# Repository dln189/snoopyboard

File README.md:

# Snoopyboard

Snoopyboard is a 4 key macro pad with a rotary encoder as well as an OLED Display, uses QMK firmware

## Features:

- 4 Mechanical keys arranged in an arrow key formation
- EC11 Rotary Encoder, controlling volume on rotation an muting when pressed
- 128x32 OLED display (still needs to be programmed whoops!)
- Seeed XIAO RP2040
- Custom PCB

## Case

The base connects to the top with 4 M3x16mm Screws, printed in 3 pieces total. (modeled in Fusion360)

Expanded view of the case: 

##PCB Design

Made in Kicad

Scematic:

PCB:

## Firmware

Snoopyboard uses QMK firmware for everything. 

- the rotary encoder changes volume. press to mute
- The 4 keys currently pause/play music, skip or go to previous song and presses right ctrl (my keybind for muting on discord)
- The OLED will be snoopy but that is currently not finished

## BOM:
Here should be everything you need to make this hackpad

- 4x Cherry MX Switches
- 4x DSA Keycaps
- 4x M3x5x4 Heatset inserts
- 4x M3x16mm SHCS Bolts
- 1x 0.91" 128x32 OLED Display
- 1x EC11 Rotary Encoder
- 1x XIAO RP2040
- 1x Case (3 printed parts)

I'm still actively working on this project so expect more stuff soon!

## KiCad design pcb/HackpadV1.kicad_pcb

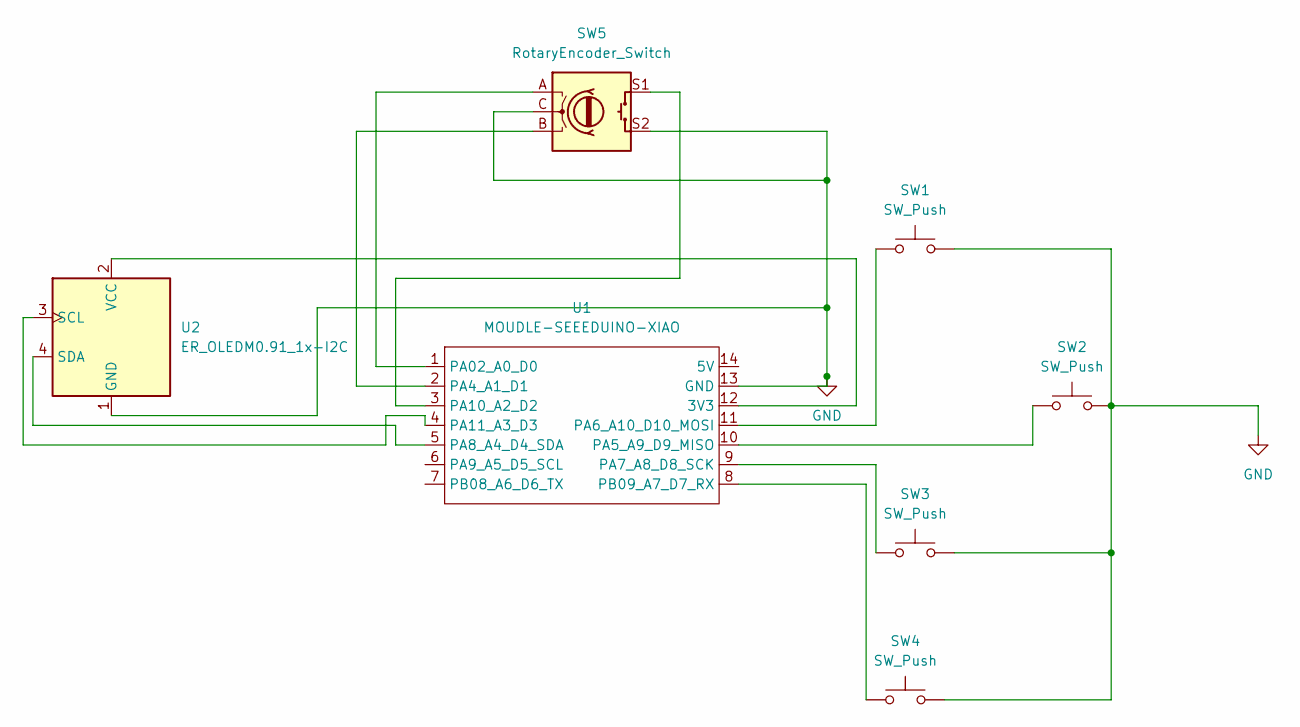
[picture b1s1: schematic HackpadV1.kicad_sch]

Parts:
SW1, SW2, SW3, SW4: SW_Push; SW_Cherry_MX_1.00u_PCB
SW5: RotaryEncoder_Switch; RotaryEncoder_Alps_EC11E-Switch_Vertical_H20mm
U1: MOUDLE-SEEEDUINO-XIAO; XIAO-Generic-Hybrid-14P-2.54-21X17.8MM
U2: ER_OLEDM0.91_1x-I2C

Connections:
GND: SW1.2, SW2.2, SW3.2, SW4.2, SW5.C, SW5.S2, U1.13 (GND), U2.1 (GND)
unnamed: U1.12 (3V3), U2.2 (VCC)
unnamed: SW5.A, U1.1 (PA02_A0_D0)
unnamed: SW5.B, U1.2 (PA4_A1_D1)
unnamed: SW2.1, U1.10 (PA5_A9_D9_MISO)
unnamed: SW1.1, U1.11 (PA6_A10_D10_MOSI)
unnamed: SW3.1, U1.9 (PA7_A8_D8_SCK)
unnamed: U1.5 (PA8_A4_D4_SDA), U2.4 (SDA)
unnamed: SW5.S1, U1.3 (PA10_A2_D2)
unnamed: U1.4 (PA11_A3_D3), U2.3 (SCL)
unnamed: SW4.1, U1.8 (PB09_A7_D7_RX)

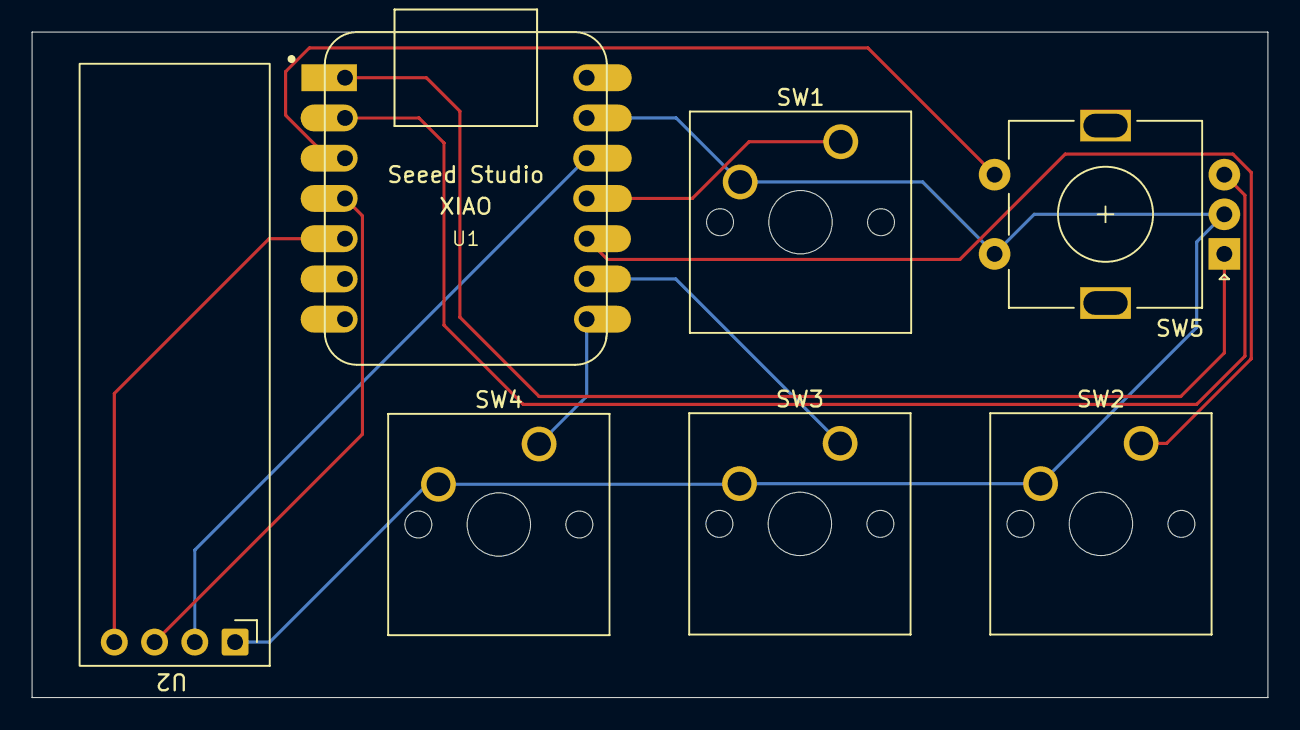
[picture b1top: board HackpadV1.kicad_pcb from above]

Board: 2 copper layers, 78.0 x 42.0 mm, 7 parts (0 on the bottom side), 11 nets.
